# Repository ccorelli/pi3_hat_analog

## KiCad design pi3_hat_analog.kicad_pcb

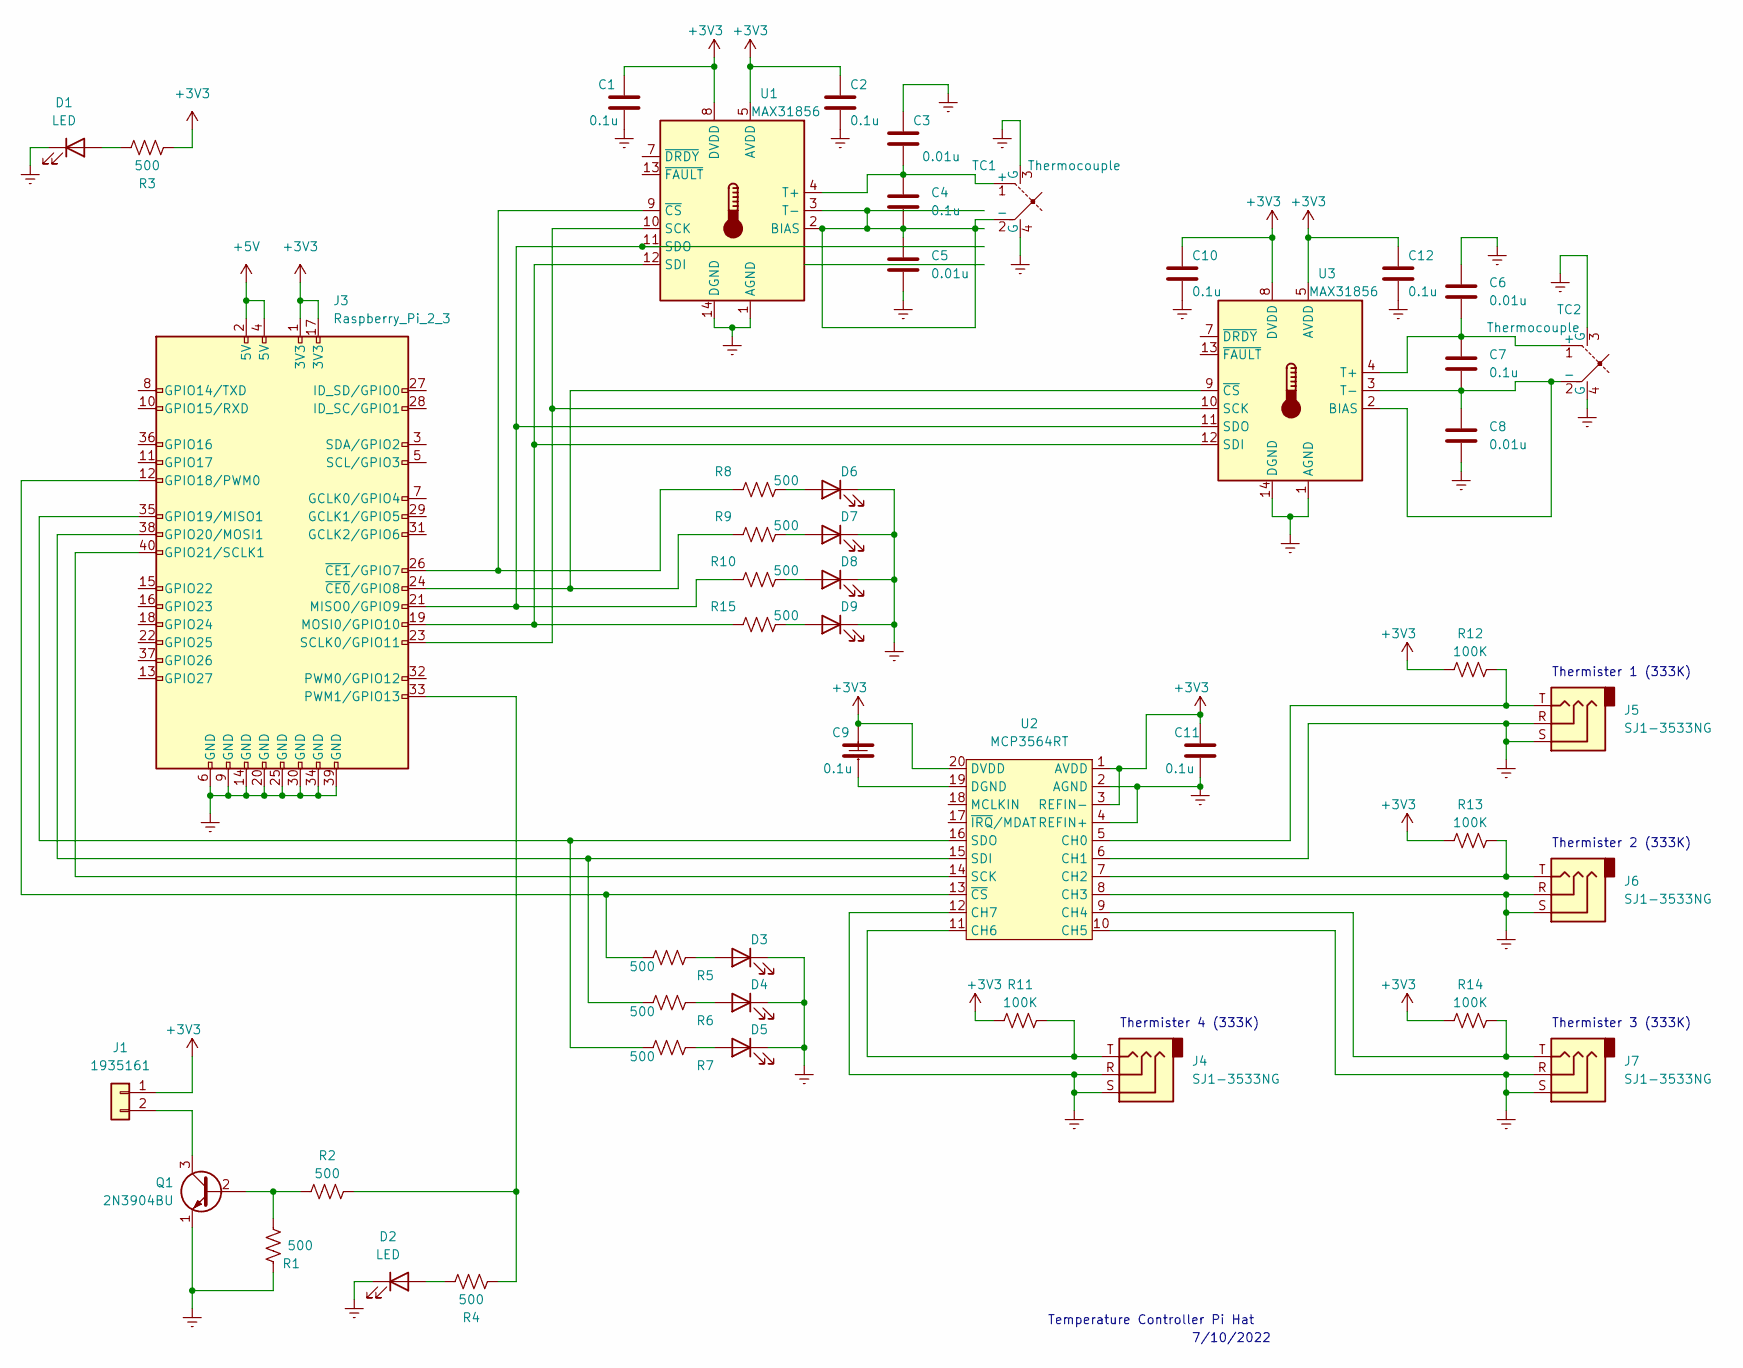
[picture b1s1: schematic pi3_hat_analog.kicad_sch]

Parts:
C1, C2, C4, C7, C9, C10, C11, C12: 0.1u; C_0603_1608Metric
C3, C5, C6, C8: 0.01u; C_0603_1608Metric
D1, D2, D3, D4, D5, D6, D7, D8, D9: LED; LED_0603_1608Metric_Pad1.05x0.95mm_HandSolder
J1: 1935161; PhoenixContact_MSTBVA_2,5_2-G_1x02_P5.00mm_Vertical
J3: Raspberry_Pi_2_3; PinHeader_2x20_P2.54mm_Vertical
J4, J5, J6, J7: SJ1-3533NG; Jack_3.5mm_CUI_SJ1-3533NG_Horizontal
Q1: 2N3904BU; TO-92_Inline
R1, R2, R3, R4, R5, R6, R7, R8, R9, R10, R15: 500; R_0603_1608Metric_Pad0.98x0.95mm_HandSolder
R11, R12, R13, R14: 100K; R_0603_1608Metric_Pad0.98x0.95mm_HandSolder
TC1, TC2: Thermocouple; thermocouple
U1, U3: MAX31856; TSSOP-14_4.4x5mm_P0.65mm
U2: MCP3564RT; TSSOP-20_4.4x6.5mm_P0.65mm

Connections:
+3V3: C1.1, C2.1, C9.1, C10.1, C11.1, C12.1, J1.1, J3.1 (3V3), J3.17 (3V3), R3.1, R11.1, R12.1, R13.1, R14.1, U1.5 (AVDD), U1.8 (DVDD), U2.1 (AVDD), U2.3 (REFIN-), U2.20 (DVDD), U3.5 (AVDD), U3.8 (DVDD)
+5V: J3.2 (5V), J3.4 (5V)
GNDREF: C1.2, C2.2, C3.1, C5.2, C6.1, C8.2, C10.2, C11.2, C12.2, D1.1 (K), D2.1 (K), D3.1 (K), D4.1 (K), D5.1 (K), D6.1 (K), D7.1 (K), D8.1 (K), D9.1 (K), J3.6 (GND), J3.9 (GND), J3.14 (GND), J3.20 (GND), J3.25 (GND), J3.30 (GND), J3.34 (GND), J3.39 (GND), J4.R, J4.S, J5.R, J5.S, J6.R, J6.S, J7.R, J7.S, Q1.1 (E), R1.2, TC1.3 (G), TC1.4 (G), TC2.3 (G), TC2.4 (G), U1.1 (AGND), U1.14 (DGND), U2.2 (AGND), U2.4 (REFIN+), U2.6 (CH1), U2.8 (CH3), U2.10 (CH5), U2.12 (CH7), U3.1 (AGND), U3.14 (DGND)
unnamed: C3.2, C4.1, TC1.1 (+), U1.4 (T+)
unnamed: C4.2, C5.1, TC1.2 (-), U1.2 (BIAS), U1.3 (T-)
unnamed: C6.2, C7.1, TC2.1 (+), U3.4 (T+)
unnamed: C7.2, C8.1, TC2.2 (-), U3.2 (BIAS), U3.3 (T-)
unnamed: C9.2, U2.19 (DGND)
unnamed: D3.2 (A), R5.1
unnamed: D4.2 (A), R6.1
unnamed: D5.2 (A), R7.1
unnamed: D6.2 (A), R8.2
unnamed: D7.2 (A), R9.2
unnamed: D8.2 (A), R10.2
unnamed: D9.2 (A), R15.2
unnamed: J1.2, Q1.3 (C)
unnamed: J3.12 (GPIO18/PWM0), R5.2, U2.13 (~CS)
unnamed: J3.19 (MOSI0/GPIO10), R15.1, U1.12 (SDI), U3.12 (SDI)
unnamed: J3.21 (MISO0/GPIO9), R10.1, U1.11 (SDO), U3.11 (SDO)
unnamed: J3.23 (SCLK0/GPIO11), U1.10 (SCK), U3.10 (SCK)
unnamed: J3.24 (~CE0/GPIO8), R9.1, U3.9 (~CS)
unnamed: J3.26 (~CE1/GPIO7), R8.1, U1.9 (~CS)
unnamed: J3.33 (PWM1/GPIO13), R2.2, R4.1
unnamed: J3.35 (GPIO19/MISO1), R7.2, U2.16 (SDO)
unnamed: J3.38 (GPIO20/MOSI1), R6.2, U2.15 (SDI)
unnamed: J3.40 (GPIO21/SCLK1), U2.14 (SCK)
unnamed: J4.T, R11.2, U2.11 (CH6)
unnamed: J5.T, R12.2, U2.5 (CH0)
unnamed: J6.T, R13.2, U2.7 (CH2)
unnamed: J7.T, R14.2, U2.9 (CH4)
unnamed: Q1.2 (B), R1.1, R2.1
unnamed: D1.2 (A), R3.2
unnamed: D2.2 (A), R4.2

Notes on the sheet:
Thermister 2 (333K)
Temperature Controller Pi Hat
Thermister 1 (333K)
Thermister 4 (333K)
Thermister 3 (333K)
7/10/2022

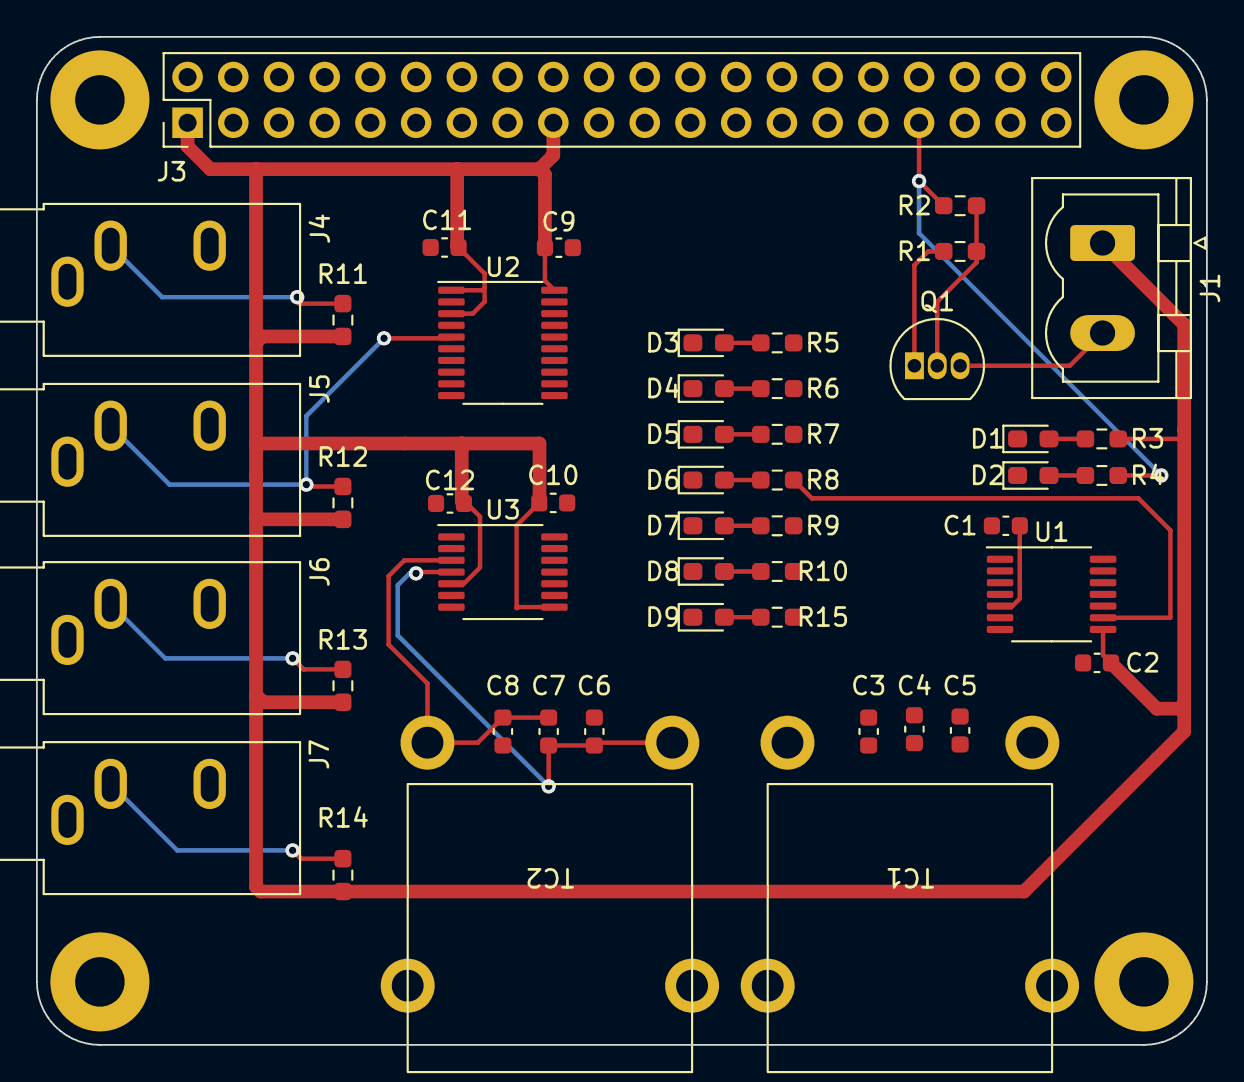
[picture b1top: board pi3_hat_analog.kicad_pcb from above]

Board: 2 copper layers, 65.0 x 56.0 mm, 48 parts (0 on the bottom side), 33 nets.

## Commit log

2023-02-13 added thermister connections to A2D
2023-02-15 added relay connector
2023-02-17 added footprints for relay circuit
2023-03-12 added thermocouple footprint. Initial board layout.
2023-03-12 added leds
2023-03-13 more placement
2023-03-13 initial component placement complete
2023-03-18 traces in progress
